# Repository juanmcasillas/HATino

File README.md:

# HATino
Head tracking using ARDUINO and BLUETOOTH reusing code from HATIRE, using GY-521 breakout board (MPU-6050) and HC-05 breakout board for
bluetooth communications. The system is powered by standard AA-batteries, so it's a complete standalone solution.

This project is aimed to create a head tracking system based on code released by FuraX49 for the HATIRE plugin for OpenTRACK.

OpenTRACK is an OpenSource project focused on head tracking for MSWindows, Linux and Apple OSX. 
Manages multiple tracking sources and support multiple outputs. See https://github.com/opentrack/opentrack
for more details.

HATino provides a full solution (hardware and software) for a head tracking system based on arduino,
using bluetooth as comunication layer, in order to avoid "wires". HATino is implemented on an
ARDUINO MICRO, with a custom PCB Board, using GY-521 IMU breakout board for gyro information, and
HC-05 bluetooth breakout board for communications. The project includes both hardware (schematics,
pcb HOW-TO info) and software (ARDUINO custom firmware and modifications, Bluetooth layer) in order
to get a complete, OpenSource system. The software is based on FuraX49' code, and some of the 
examples on i2clib for arduino.

Libraries:

I2Cdev			https://github.com/jrowberg/i2cdevlib.git

Wire			(included)

SoftwareSerial	(included)

For information on installing libraries, see: http://arduino.cc/en/Guide/Libraries

Based on hatire source code (by FuraX49):

http://sourceforge.net/projects/hatire/files/ARDUINO/MPU6050/HAT_100.ino/download

LocalFile                       GIT
-----------------------------------------------------------------------------------------
HAT_gy521_wip_bt.ino            HATino.ino

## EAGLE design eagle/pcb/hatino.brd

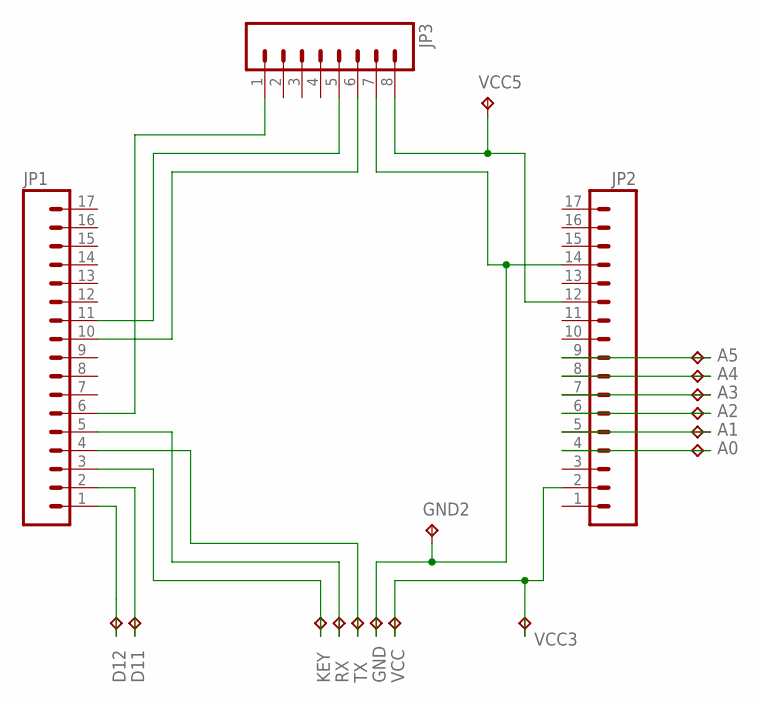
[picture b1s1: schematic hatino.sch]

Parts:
A0, A1, A2, A3, A4, A5: TPPAD1-13Y; P1-13Y
D11, D12: TPPAD1-13Y; P1-13Y
GND, GND2: TPPAD1-13Y; P1-13Y
JP1, JP2: M17; 1X17
JP3: M08; 1X08_ROUND
KEY: TPPAD1-13Y; P1-13Y
RX: TPPAD1-13Y; P1-13Y
TX: TPPAD1-13Y; P1-13Y
VCC, VCC3, VCC5: TPPAD1-13Y; P1-13Y

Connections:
unnamed: D12.TP, JP1.1
unnamed: JP2.2, VCC.TP, VCC3.TP
unnamed: D11.TP, JP1.2
unnamed: A0.TP, JP2.4
unnamed: A1.TP, JP2.5
unnamed: A2.TP, JP2.6
unnamed: A3.TP, JP2.7
unnamed: A4.TP, JP2.8
unnamed: A5.TP, JP2.9
unnamed: JP2.12, JP3.8, VCC5.TP
unnamed: GND.TP, GND2.TP, JP2.14, JP3.7
unnamed: JP1.5, RX.TP
unnamed: JP1.6, JP3.1
unnamed: JP1.4, TX.TP
unnamed: JP1.10, JP3.6
unnamed: JP1.11, JP3.5
unnamed: JP1.3, KEY.TP

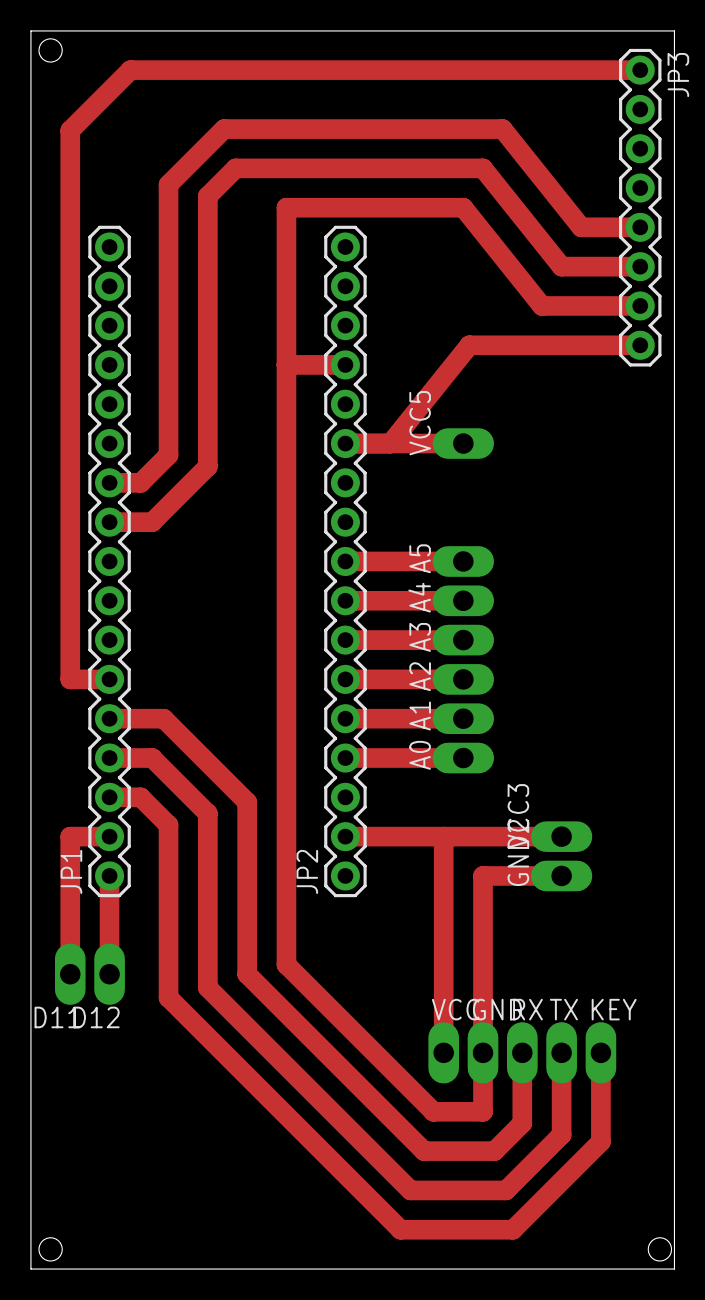
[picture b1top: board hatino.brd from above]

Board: 2 copper layers, 41.6 x 80.0 mm, 19 parts (0 on the bottom side), 17 nets.

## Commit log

2016-01-04 Update README.md
    Added more info about project
2016-01-04 Added preliminary library info
2016-01-04 Added PCB schematics for EAGLE. Added printable PDF file to create the PCB directly. Added EAGLE libraries
2016-01-04 initial original source code HAT_100.ino from FuraX49. see:
    http://sourceforge.net/projects/hatire/files/ARDUINO/MPU6050/HAT_100.ino/download
    for original source code and more information.
2016-01-04 WIP code for HATino. This version works with OpenTrack 2.3-rc21p1. Not for production use.
2016-01-04 WIP doc
2022-02-21 fixing the issue #1 opened by TSPitFire

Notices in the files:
parts and their libraries:
SparkFun-Connectors: Licensing: Creative Commons ShareAlike 4.0 International - https://creativecommons.org/licenses/by-sa/4.0
